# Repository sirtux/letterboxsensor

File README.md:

# LoRaWAN EU868Mhz Letterbox Sensor

sensing letters in your letterbox via two infrared proximity sensors (HSDL9100),
sending out status via lora / lorawan, using RAK3172 (based on STM32WLE5CC) CPU/RF, powered by a CR2032 battery.

This project is a remake of https://github.com/hierle/letterbox-sensor-v2/, many thanks to the original author!

This design is built in a way, that it can be assembled by a factory house like JLCPCB and you do not need
to fiddle around with soldering small components - especially the HSDL9100 are very fiddly.

Contents:

- ./letterboxsensor/		kicad design files
- ./jlclib/			library files for non standard components
- ./ttn/			Tools to setup TheThingsNetwork
- ./arduino/			Source Code for the sensor
- ./gerber/			Required files for PCB manufacturing
- ./jlcassembly/		Files for JLC Assembly Service

Features:
- using RAKWireless RAK3172 based on STM32WLE5CC
- deep sleep at (measured) 5uA including battery voltage divider and tantalium caps
- two proximity sensors HSDL9100
- USB-C interface for flashing and serial monitor, via FT230XS-R USB-UART
- onboard 868MHz PCB antenna after TI document http://www.ti.com/lit/an/swra227e/swra227e.pdf
- lorawan activation either ABP or OTAA
- battery voltage measurment thru voltage divider (2x 10MOhm)

RAK3172 documentation:

https://docs.rakwireless.com/Product-Categories/WisDuo/RAK3172-Module/Overview/

How to compile:

Follow the instructions on<br>
https://docs.rakwireless.com/Product-Categories/WisDuo/RAK3172-Module/Quickstart/<br>
in short:<br>
- install ArduinoIDE from arduino.cc
- add the following URL to the boards manager URLs section in preferences:
https://raw.githubusercontent.com/RAKWireless/RAKwireless-Arduino-BSP-Index/main/package_rakwireless.com_rui_index.json
- install the "RAKwireless RUI STM32 Boards" from the Boards Manager
- select "WisDuo RAK3172 Evaluation Board" board
- on Mac you might need to install pyserial: sudo pip3 install pyserial
- on Linux you might need to install python3-pyserial
- connect the board, make sure it's powered on (DIP switch)
- select the corresponding serial port
- open the sketch folder
- adjust config.h and lorawan.h
- compile and flash

For configuration adjust config.h and lorawan.h

config.h:
- PERIOD: the time intervall you want the sensor to send it's data, in minutes, default is 30 minutes
- THRESHOLD: the threshold for the sensor readings (empty/full), can later be "overwritten" in e.g. HTML integration
- USE_OTAA: if true, OTAA will be used instead of ABP, so we do not have to worry about frame counters after reset / battery change
- DATARATE and TXPOWER: adjust to your needs, your packets should be reliably received, w/o wasting to much power
- see also the comments for each entry in config.h

lorawan.h:
- set your lorawan keys for either ABP or OTAA
- OTAA_APPEUI or JOINEUI is only needed to select a specific JOIN server, in private networks can be set to any value

Additional notes:
- you will need a *DATA* USB-C cable, a charging only cable will not work, as it's missing the data pins ;-)
- the DIP switch allows to power the device directly from USB, but when using the battery in production environment (letterbox), it should be switched off, not to waist power on the FT230 USB-UART chip

Letterbox sensor v2 lorawan payload package byte structure:

|byte|    0     |  1   2 | 3   4 | 5   6 |    7    |
|----|----------|--------|-------|-------|---------|
|    |0x00=empty|battery |sensor1|sensor2|threshold|
|    |0xFF=full |voltage |raw    |raw    |         |

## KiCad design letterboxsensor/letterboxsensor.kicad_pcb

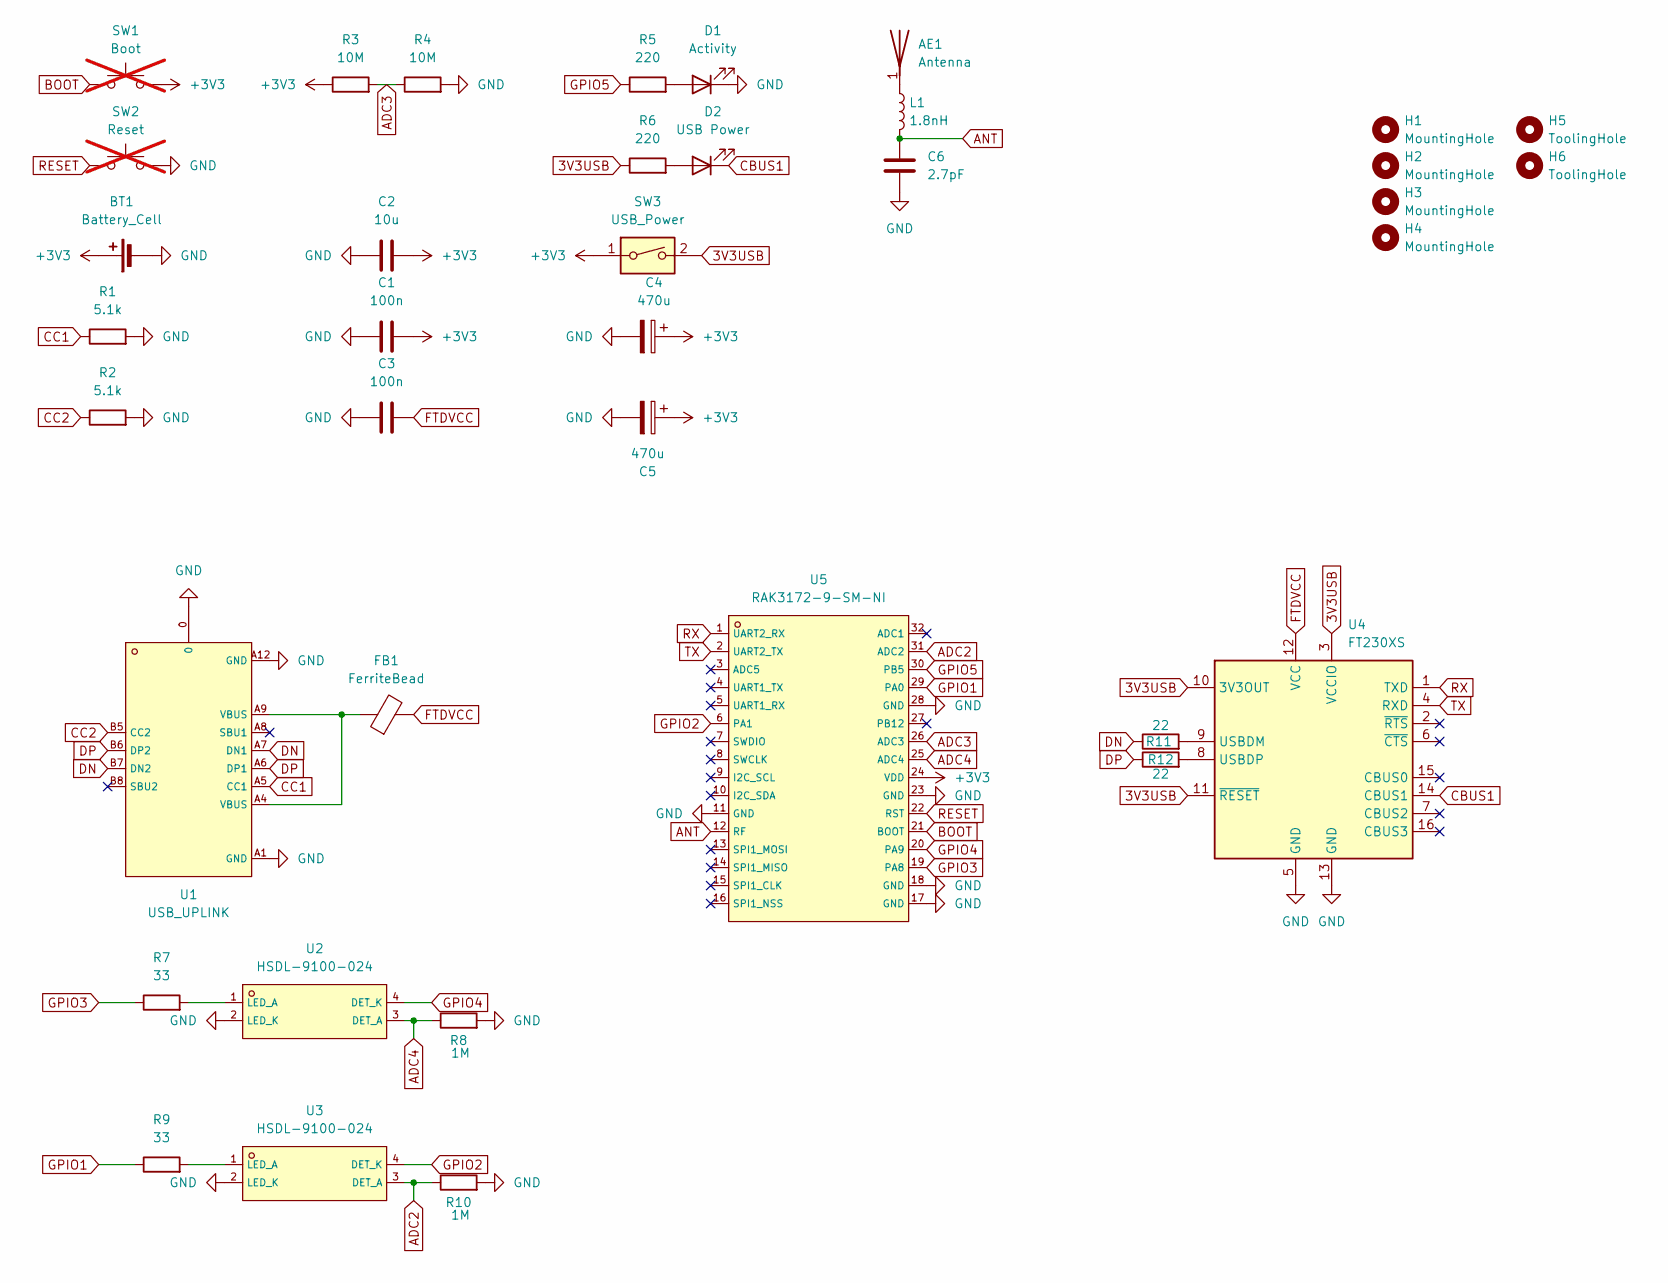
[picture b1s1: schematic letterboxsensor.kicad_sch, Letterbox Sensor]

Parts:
AE1: Antenna; TI-DN024-SL
BT1: Battery_Cell; BAT-TH_CR2032-BS-6-1; LCSC C70377
C1, C3: 100n; C_0805_2012Metric_Pad1.18x1.45mm_HandSolder; LCSC C49678
C2: 10u; C_0805_2012Metric_Pad1.18x1.45mm_HandSolder; LCSC C440198
C4, C5: 470u; CP_EIA-7343-43_Kemet-X_Pad2.25x2.55mm_HandSolder; LCSC C7234
C6: 2.7pF; C_0805_2012Metric_Pad1.18x1.45mm_HandSolder; LCSC C1803
D1: Activity; LED0805-R-RD; LCSC C2297
D2: USB Power; LED0805-R-RD; LCSC C2297
FB1: FerriteBead; R_0805_2012Metric_Pad1.20x1.40mm_HandSolder; LCSC C1017
H1, H2, H3, H4: MountingHole; MountingHole_2.2mm_M2_ISO7380
H5, H6: ToolingHole; ToolingHole_JLCSMT
L1: 1.8nH; L_0805_2012Metric; LCSC C578016
R1, R2: 5.1k; R_0805_2012Metric_Pad1.20x1.40mm_HandSolder; LCSC C27834
R3, R4: 10M; R_0603_1608Metric_Pad0.98x0.95mm_HandSolder; LCSC C7250
R5, R6: 220; R_0805_2012Metric_Pad1.20x1.40mm_HandSolder; LCSC C17557
R7, R9: 33; R_0805_2012Metric_Pad1.20x1.40mm_HandSolder; LCSC C17634
R8, R10: 1M; R_0805_2012Metric_Pad1.20x1.40mm_HandSolder; LCSC C17514
R11, R12: 22; R_0805_2012Metric_Pad1.20x1.40mm_HandSolder; LCSC C17561
SW1: Boot; SW-TH_4P-L6.0-W6.0-P4.50-LS6.5; LCSC C13828; not fitted
SW2: Reset; SW-TH_4P-L6.0-W6.0-P4.50-LS6.5; LCSC C13828; not fitted
SW3: USB_Power; SW-SMD_DSIC01LSGET; LCSC C54948
U1: USB_UPLINK; USB-C-SMD_TYPE-C-USB-17; LCSC C167321
U2, U3: HSDL-9100-024; OPTO-SMD_HSDL-9100-024; LCSC C5186960
U4: FT230XS; SSOP-16_3.9x4.9mm_P0.635mm; LCSC C69082
U5: RAK3172-9-SM-NI; WIRELM-SMD_32P-L15.5-W15.0-P1.00; LCSC C18548052

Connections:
3V3USB: R6.1, SW3.2, U4.3 (VCCIO), U4.10 (3V3OUT), U4.11 (~RESET)
+3V3: BT1.1 (+), C1.2, C2.2, C4.1, C5.1, R3.1, SW1.2, SW3.1, U5.24 (VDD)
ADC2: R10.1, U3.3 (DET_A), U5.31 (ADC2)
ADC3: R3.2, R4.1, U5.26 (ADC3)
ADC4: R8.1, U2.3 (DET_A), U5.25 (ADC4)
ANT: C6.1, L1.2, U5.12 (RF)
BOOT: SW1.1, U5.21 (BOOT)
CBUS1: D2.1 (K), U4.14 (CBUS1)
CC1: R1.1, U1.A5 (CC1)
CC2: R2.1, U1.B5 (CC2)
DN: R11.1, U1.A7 (DN1), U1.B7 (DN2)
DP: R12.1, U1.A6 (DP1), U1.B6 (DP2)
FTDVCC: C3.2, FB1.2, U4.12 (VCC)
GND: BT1.2 (-), C1.1, C2.1, C3.1, C4.2, C5.2, C6.2, D1.1 (K), R1.2, R2.2, R4.2, R8.2, R10.2, SW2.2, U1.0, U1.A1 (GND), U1.A12 (GND), U2.2 (LED_K), U3.2 (LED_K), U4.5 (GND), U4.13 (GND), U5.11 (GND), U5.17 (GND), U5.18 (GND), U5.23 (GND), U5.28 (GND)
GPIO1: R9.1, U5.29 (PA0)
GPIO2: U3.4 (DET_K), U5.6 (PA1)
GPIO3: R7.1, U5.19 (PA8)
GPIO4: U2.4 (DET_K), U5.20 (PA9)
GPIO5: R5.1, U5.30 (PB5)
unnamed: AE1.1 (A), L1.1
unnamed: D1.2 (A), R5.2
unnamed: D2.2 (A), R6.2
unnamed: FB1.1, U1.A4 (VBUS), U1.A9 (VBUS)
unnamed: R7.2, U2.1 (LED_A)
unnamed: R9.2, U3.1 (LED_A)
unnamed: R11.2, U4.9 (USBDM)
unnamed: R12.2, U4.8 (USBDP)
RESET: SW2.1, U5.22 (RST)
RX: U4.1 (TXD), U5.1 (UART2_RX)
TX: U4.4 (RXD), U5.2 (UART2_TX)

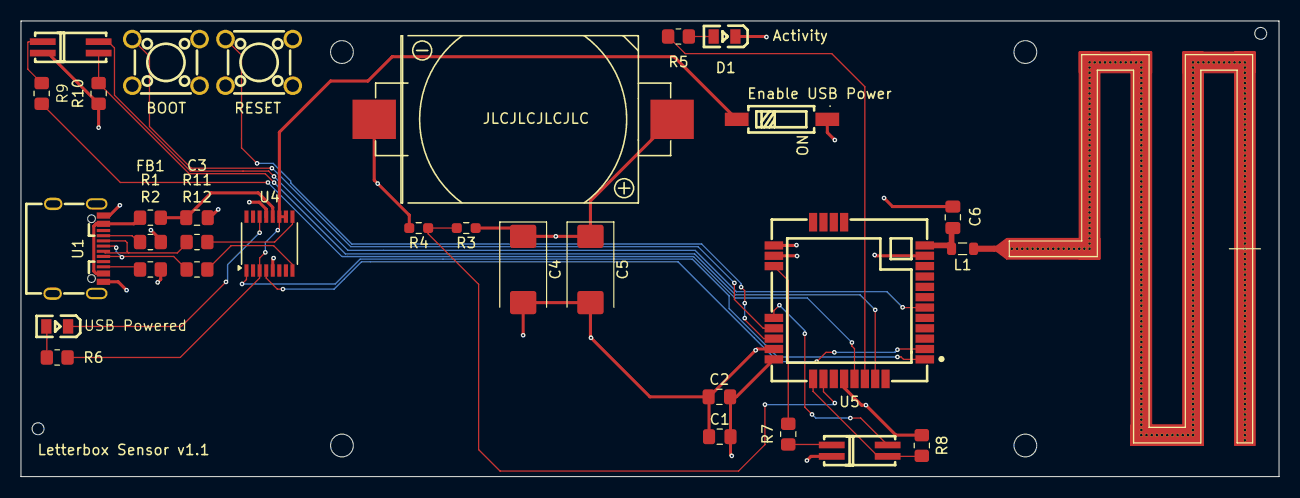
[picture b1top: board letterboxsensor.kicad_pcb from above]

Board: 4 copper layers, 121.5 x 44.0 mm, 38 parts (0 on the bottom side), 30 nets.

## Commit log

2024-08-17 Added KiCad .gitignore
2024-08-17 Release v1.1
2024-08-17 Updated the PCB rendering
2024-08-17 Remove broken debug file
